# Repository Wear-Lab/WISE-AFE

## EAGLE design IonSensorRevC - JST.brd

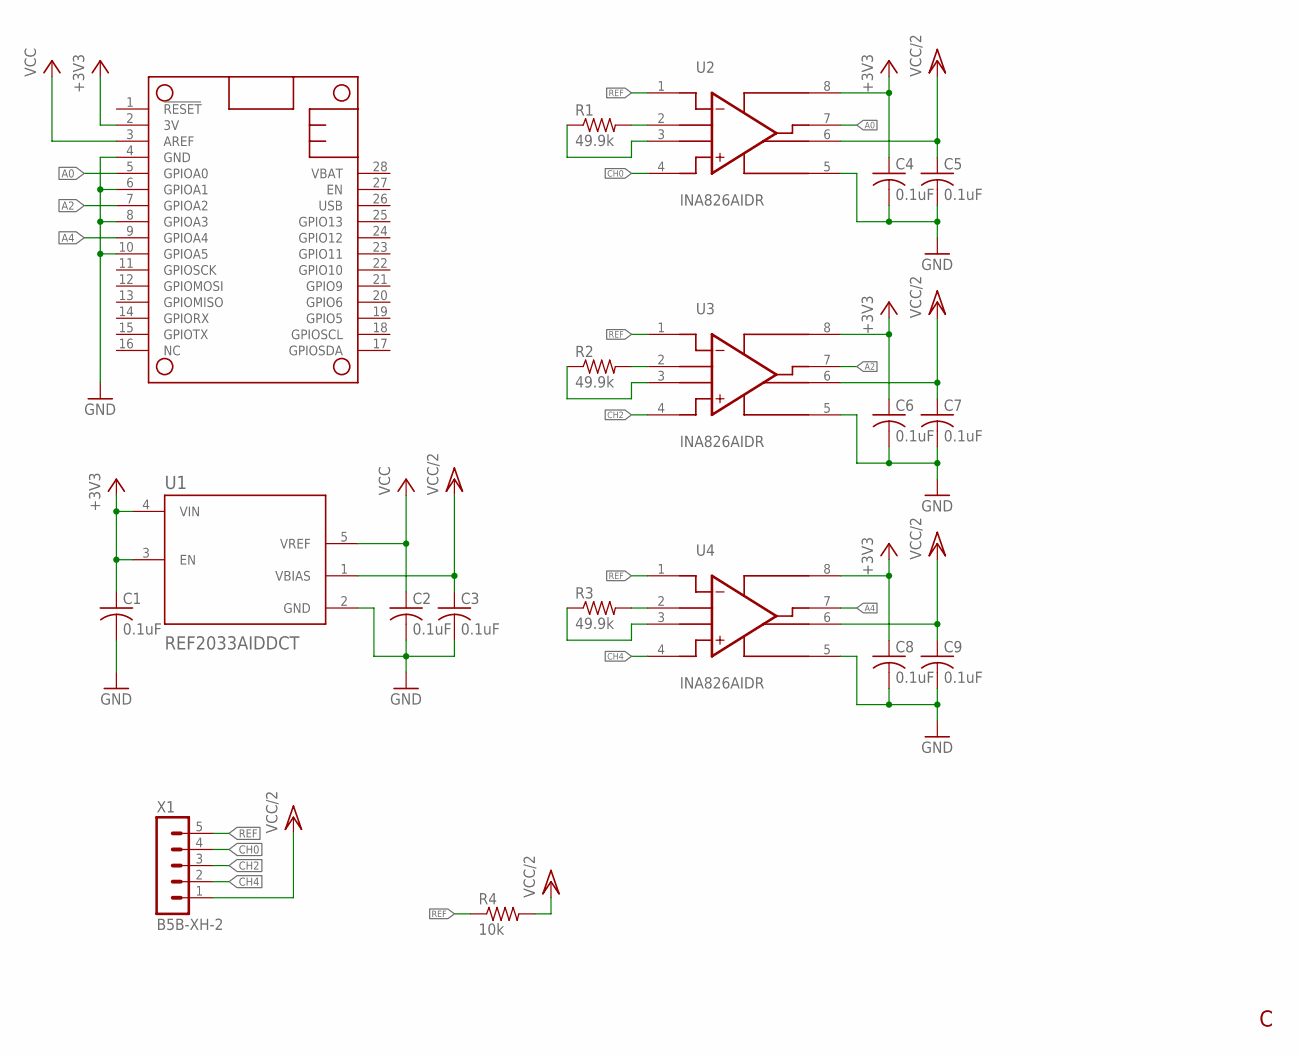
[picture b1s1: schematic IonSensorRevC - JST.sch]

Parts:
C1, C2, C3, C4, C5, C6, C7, C8, C9: 0.1uF; C0402
MS1: FEATHERWING
R1, R2, R3: 49.9k; R0402
R4: 10k; R0402
U1: REF2033AIDDCT; SOT95P280X110-5N
U2, U3, U4: INA826AIDR; SOIC127P599X175-8N
X1: B5B-XH-2; B5B-XH-A

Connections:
+3V3: C1.1, C4.1, C6.1, C8.1, MS1.2 (3V), U1.3 (EN), U1.4 (VIN), U2.8 (+VS), U3.8 (+VS), U4.8 (+VS)
A0: MS1.5 (GPIOA0), U2.7 (VOUT)
A2: MS1.7 (GPIOA2), U3.7 (VOUT)
A4: MS1.9 (GPIOA4), U4.7 (VOUT)
CH0: U2.4 (+IN), X1.4
CH2: U3.4 (+IN), X1.3
CH4: U4.4 (+IN), X1.2
GND: C1.2, C2.2, C3.2, C4.2, C5.2, C6.2, C7.2, C8.2, C9.2, MS1.4 (GND), MS1.6 (GPIOA1), MS1.8 (GPIOA3), MS1.10 (GPIOA5), U1.2 (GND), U2.5 (-VS), U3.5 (-VS), U4.5 (-VS)
unnamed: R1.2, U2.2 (RG_2)
unnamed: R1.1, U2.3 (RG_3)
unnamed: R2.2, U3.2 (RG_2)
unnamed: R2.1, U3.3 (RG_3)
unnamed: R3.2, U4.2 (RG_2)
unnamed: R3.1, U4.3 (RG_3)
REF: R4.1, U2.1 (-IN), U3.1 (-IN), U4.1 (-IN), X1.5
VCC: C2.1, MS1.3 (AREF), U1.5 (VREF)
VCC/2: C3.1, C5.1, C7.1, C9.1, R4.2, U1.1 (VBIAS), U2.6 (REF), U3.6 (REF), U4.6 (REF), X1.1

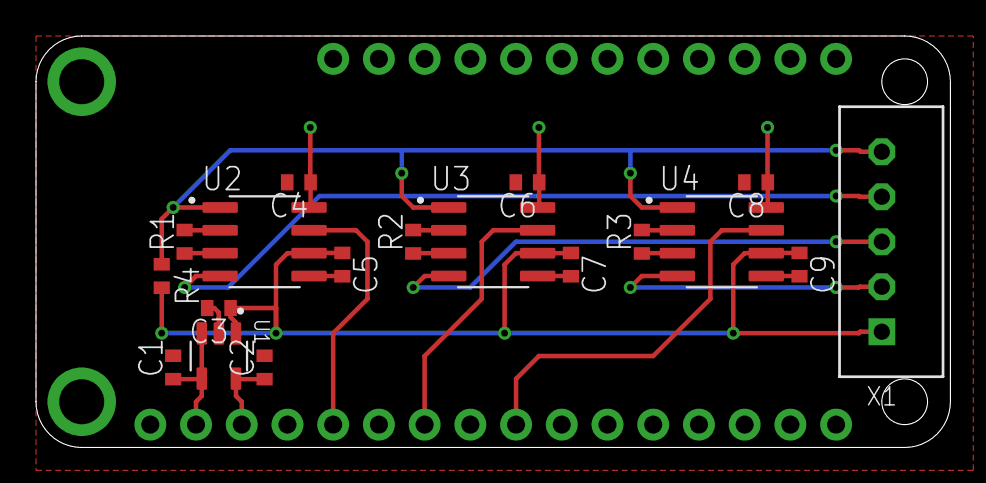
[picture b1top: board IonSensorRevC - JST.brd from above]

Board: 2 copper layers, 50.8 x 22.9 mm, 19 parts (0 on the bottom side), 17 nets.

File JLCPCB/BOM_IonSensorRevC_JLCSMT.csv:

Comment,Designator,Footprint
0.1uF,"C1, C2, C3, C4, C5, C6, C7, C8, C9",C0402
10k,R4,R0402
49.9k,"R1, R2, R3",R0402
INA826AIDR,"U2, U3, U4",SOIC127P599X175-8N
REF2033AIDDCT,U1,SOT95P280X110-5N
52745-0690,X1,52745-0690

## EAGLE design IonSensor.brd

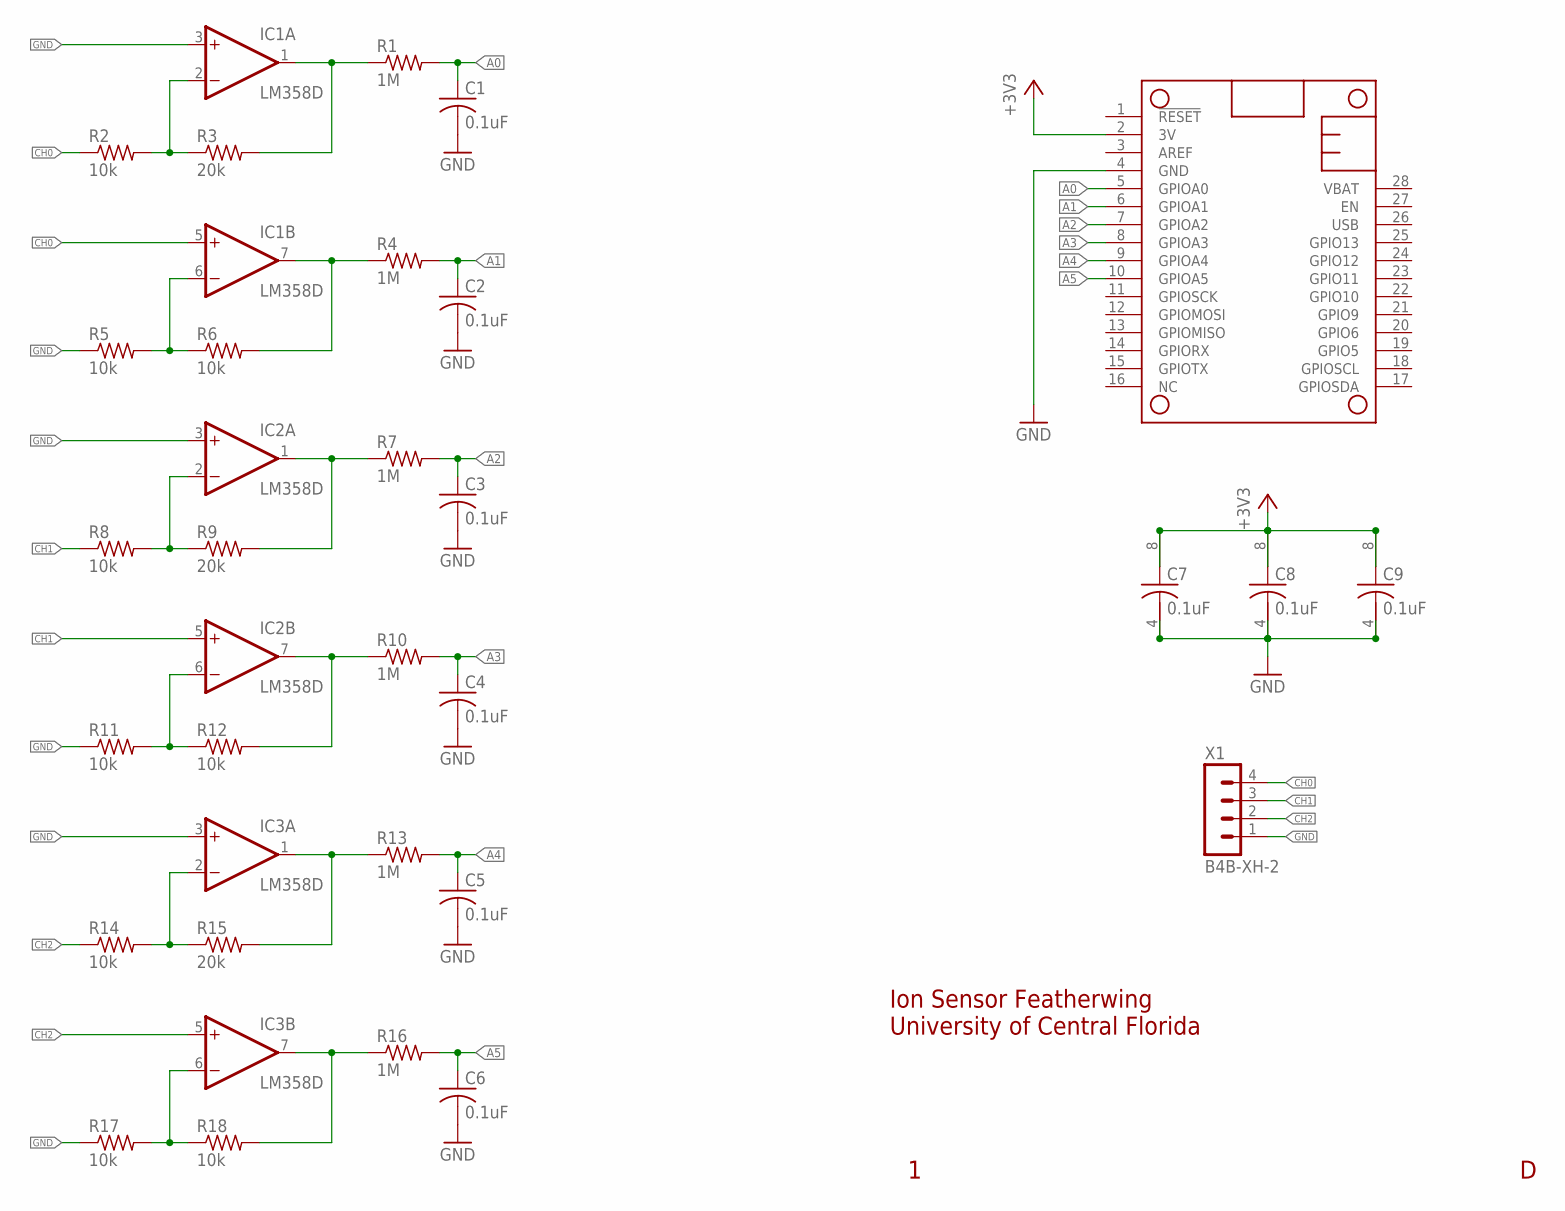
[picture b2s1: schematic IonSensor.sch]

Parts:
C1, C2, C3, C4, C5, C6, C7, C8, C9: 0.1uF; C0402
IC1, IC2, IC3: LM358D; SO08
MS1: FEATHERWING
R1, R4, R7, R10, R13, R16: 1M; R0402
R2, R5, R6, R8, R11, R12, R14, R17, R18: 10k; R0402
R3, R9, R15: 20k; R0402
X1: B4B-XH-2; B4B-XH-A

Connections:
+3V3: C7.1, C8.1, C9.1, IC1.8 (V+), IC2.8 (V+), IC3.8 (V+), MS1.2 (3V)
A0: C1.1, MS1.5 (GPIOA0), R1.2
A1: C2.1, MS1.6 (GPIOA1), R4.2
A2: C3.1, MS1.7 (GPIOA2), R7.2
A3: C4.1, MS1.8 (GPIOA3), R10.2
A4: C5.1, MS1.9 (GPIOA4), R13.2
A5: C6.1, MS1.10 (GPIOA5), R16.2
CH0: IC1.5 (+IN), R2.1, X1.4
CH1: IC2.5 (+IN), R8.1, X1.3
CH2: IC3.5 (+IN), R14.1, X1.2
GND: C1.2, C2.2, C3.2, C4.2, C5.2, C6.2, C7.2, C8.2, C9.2, IC1.3 (+IN), IC1.4 (V-), IC2.3 (+IN), IC2.4 (V-), IC3.3 (+IN), IC3.4 (V-), MS1.4 (GND), R5.1, R11.1, R17.1, X1.1
unnamed: IC1.2 (-IN), R2.2, R3.1
unnamed: IC1.6 (-IN), R5.2, R6.1
unnamed: IC1.1 (OUT), R1.1, R3.2
unnamed: IC1.7 (OUT), R4.1, R6.2
unnamed: IC2.2 (-IN), R8.2, R9.1
unnamed: IC2.1 (OUT), R7.1, R9.2
unnamed: IC2.6 (-IN), R11.2, R12.1
unnamed: IC2.7 (OUT), R10.1, R12.2
unnamed: IC3.2 (-IN), R14.2, R15.1
unnamed: IC3.1 (OUT), R13.1, R15.2
unnamed: IC3.6 (-IN), R17.2, R18.1
unnamed: IC3.7 (OUT), R16.1, R18.2

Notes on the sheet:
Ion Sensor Featherwing University of Central Florida

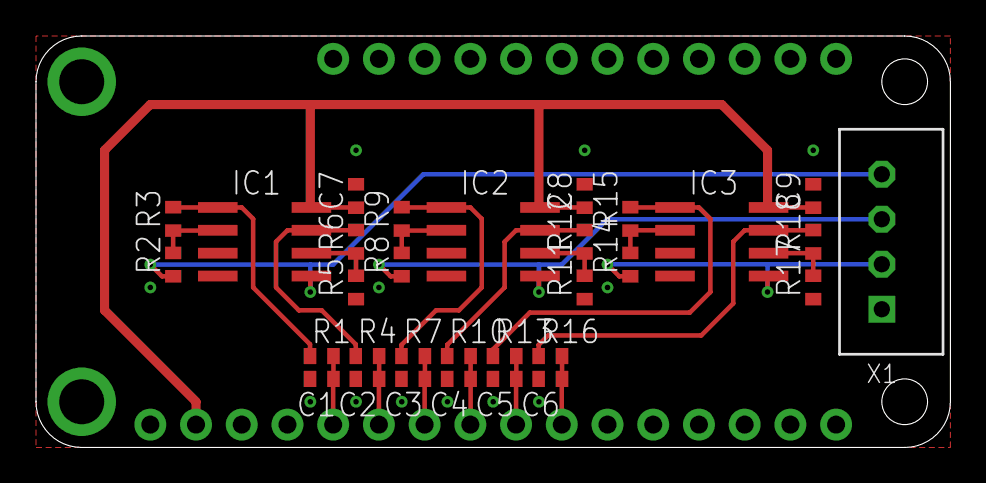
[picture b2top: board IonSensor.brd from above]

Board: 2 copper layers, 50.8 x 22.9 mm, 32 parts (0 on the bottom side), 23 nets.

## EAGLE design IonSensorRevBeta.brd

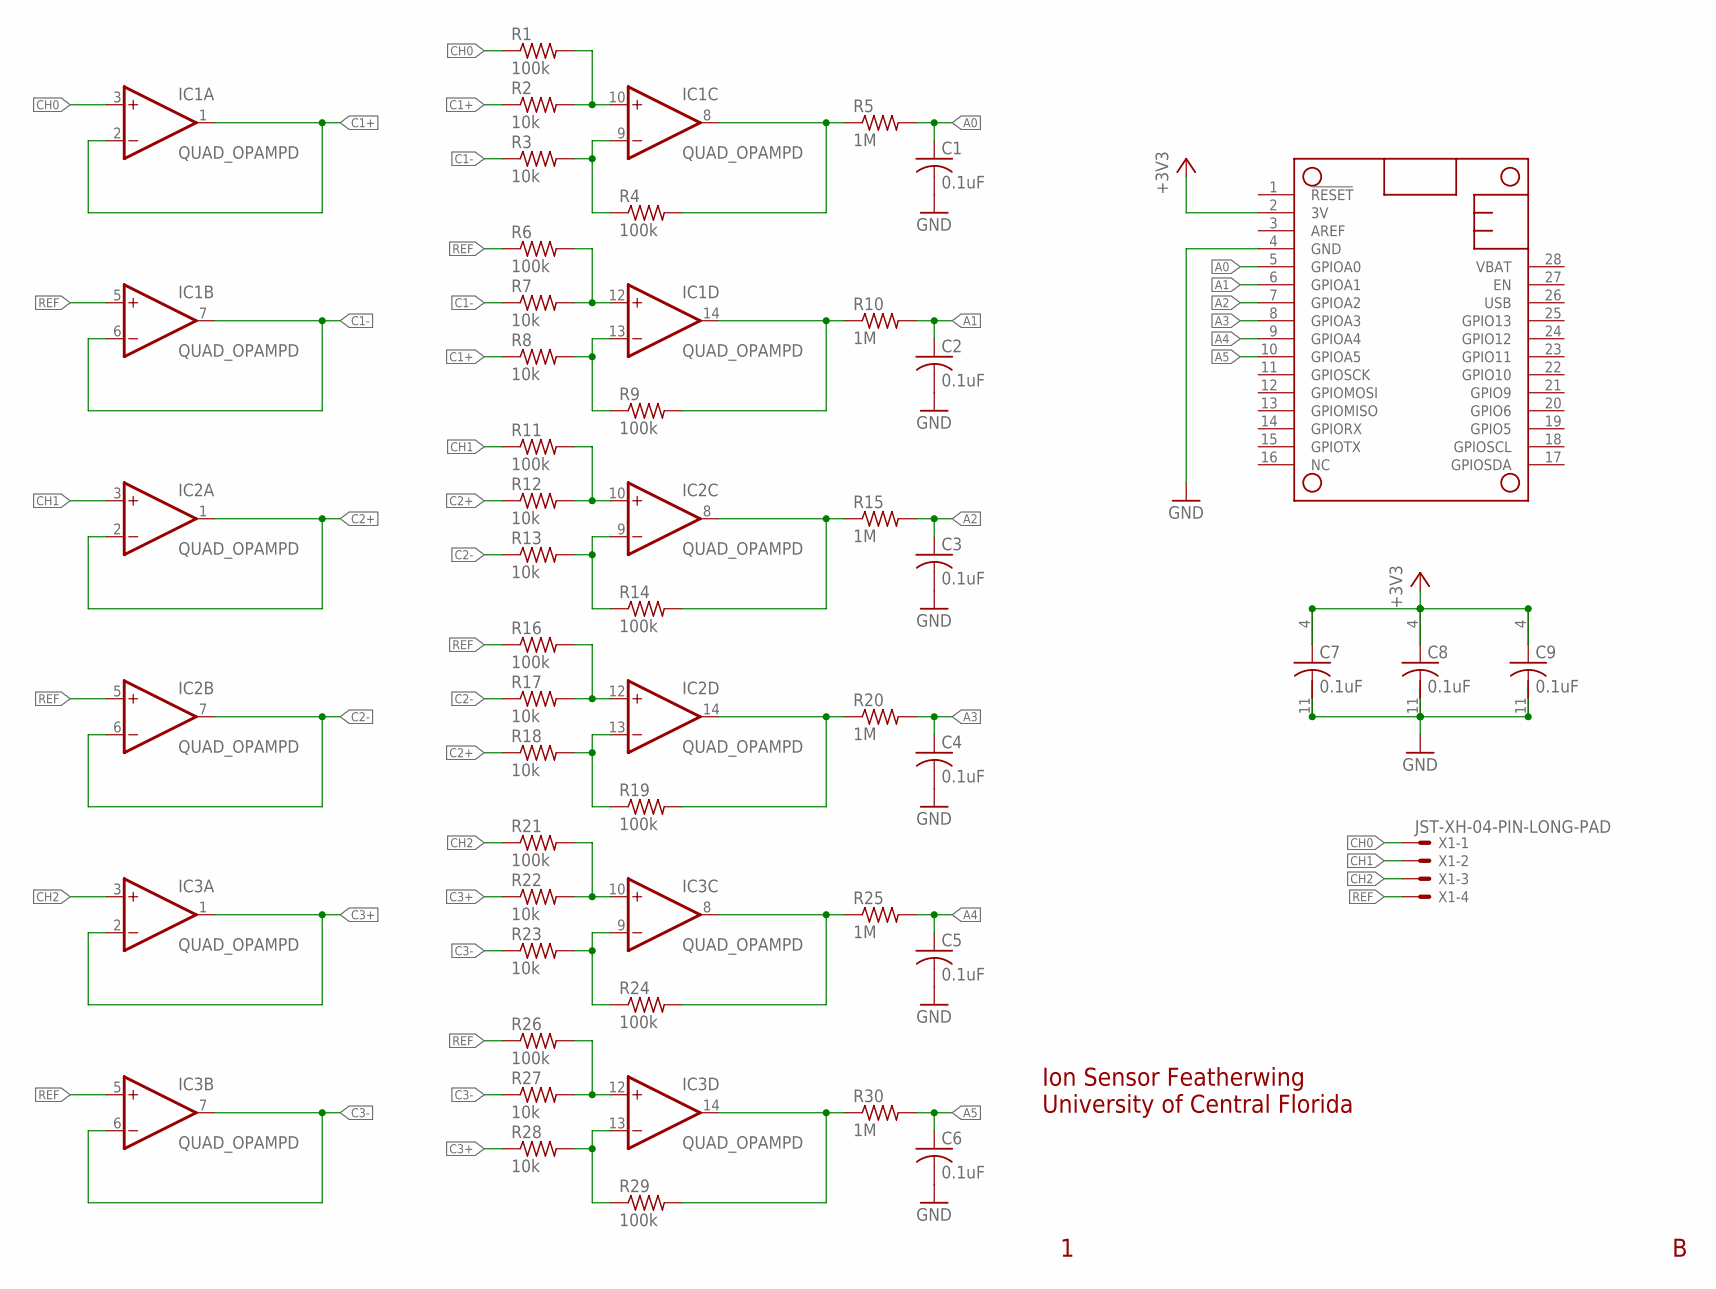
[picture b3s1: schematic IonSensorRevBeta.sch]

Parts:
C1, C2, C3, C4, C5, C6, C7, C8, C9: 0.1uF; C0402
IC1, IC2, IC3: QUAD_OPAMPD; SO14
MS1: FEATHERWING
R1, R4, R6, R9, R11, R14, R16, R19, R21, R24, R26, R29: 100k; R0402
R2, R3, R7, R8, R12, R13, R17, R18, R22, R23, R27, R28: 10k; R0402
R5, R10, R15, R20, R25, R30: 1M; R0402
X1: JST-XH-04-PIN-LONG-PAD; JST-XH-04-PACKAGE-LONG-PAD

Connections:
+3V3: C7.1, C8.1, C9.1, IC1.4 (V+), IC2.4 (V+), IC3.4 (V+), MS1.2 (3V)
A0: C1.1, MS1.5 (GPIOA0), R5.2
A1: C2.1, MS1.6 (GPIOA1), R10.2
A2: C3.1, MS1.7 (GPIOA2), R15.2
A3: C4.1, MS1.8 (GPIOA3), R20.2
A4: C5.1, MS1.9 (GPIOA4), R25.2
A5: C6.1, MS1.10 (GPIOA5), R30.2
C1+: IC1.1 (OUT), IC1.2 (-IN), R2.1, R8.1
C1-: IC1.6 (-IN), IC1.7 (OUT), R3.1, R7.1
C2+: IC2.1 (OUT), IC2.2 (-IN), R12.1, R18.1
C2-: IC2.6 (-IN), IC2.7 (OUT), R13.1, R17.1
C3+: IC3.1 (OUT), IC3.2 (-IN), R22.1, R28.1
C3-: IC3.6 (-IN), IC3.7 (OUT), R23.1, R27.1
CH0: IC1.3 (+IN), R1.1, X1.1
CH1: IC2.3 (+IN), R11.1, X1.2
CH2: IC3.3 (+IN), R21.1, X1.3
GND: C1.2, C2.2, C3.2, C4.2, C5.2, C6.2, C7.2, C8.2, C9.2, IC1.11 (V-), IC2.11 (V-), IC3.11 (V-), MS1.4 (GND)
unnamed: IC1.10 (+IN), R1.2, R2.2
unnamed: IC1.9 (-IN), R3.2, R4.1
unnamed: IC3.10 (+IN), R21.2, R22.2
unnamed: IC1.12 (+IN), R6.2, R7.2
unnamed: IC1.8 (OUT), R4.2, R5.1
unnamed: IC1.13 (-IN), R8.2, R9.1
unnamed: IC3.9 (-IN), R23.2, R24.1
unnamed: IC2.10 (+IN), R11.2, R12.2
unnamed: IC2.9 (-IN), R13.2, R14.1
unnamed: IC1.14 (OUT), R9.2, R10.1
unnamed: IC2.12 (+IN), R16.2, R17.2
unnamed: IC3.12 (+IN), R26.2, R27.2
unnamed: IC2.13 (-IN), R18.2, R19.1
unnamed: IC2.8 (OUT), R14.2, R15.1
unnamed: IC3.13 (-IN), R28.2, R29.1
unnamed: IC2.14 (OUT), R19.2, R20.1
unnamed: IC3.8 (OUT), R24.2, R25.1
unnamed: IC3.14 (OUT), R29.2, R30.1
REF: IC1.5 (+IN), IC2.5 (+IN), IC3.5 (+IN), R6.1, R16.1, R26.1, X1.4

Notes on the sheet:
Ion Sensor Featherwing University of Central Florida

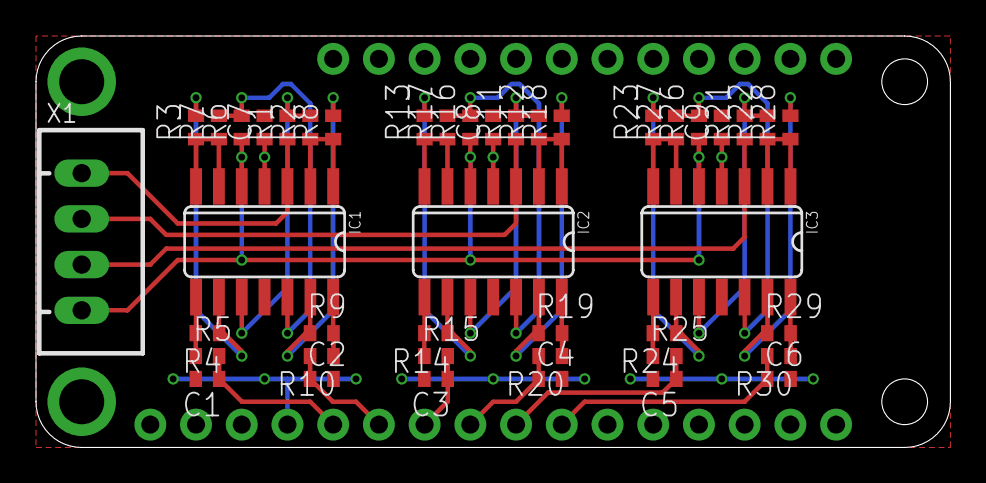
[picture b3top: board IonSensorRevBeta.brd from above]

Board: 2 copper layers, 50.8 x 22.9 mm, 44 parts (0 on the bottom side), 36 nets.

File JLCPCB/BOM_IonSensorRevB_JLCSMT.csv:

Comment,Designator,Footprint
0.1uF,"C1,C2,C3,C4,C5,C6,C7,C8,C9",C0402
100k,"R1,R4,R6,R9,R11,R14,R16,R19,R21,R24,R26,R29",R0402
10k,"R2,R3,R7,R8,R12,R13,R17,R18,R22,R23,R27,R28",R0402
1M,"R5,R10,R15,R20,R25,R30",R0402
QUAD_OPAMPD,"IC1,IC2,IC3",SO14
F0500WR-S-04PNLNG1GT0R,X1,F0500WR-S-04PNLNG1GT0R

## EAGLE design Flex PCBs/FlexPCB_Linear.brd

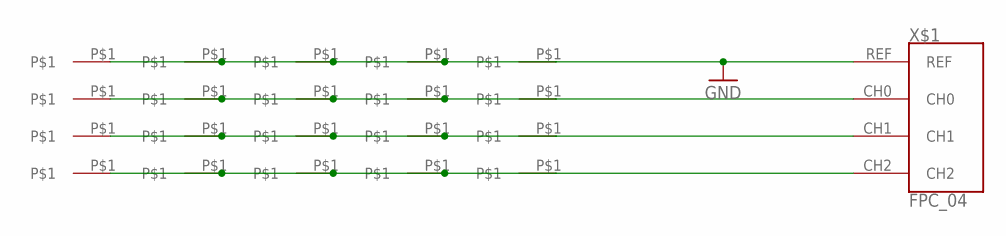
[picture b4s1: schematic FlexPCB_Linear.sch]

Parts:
U$1, U$2, U$3, U$4, U$5, U$6, U$7, U$8, U$9, U$10, U$11, U$12, U$13, U$14, U$15, U$16, U$17, U$18, U$19, U$20: CONN
X$1: FPC_04

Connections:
GND: U$1.P$1, U$5.P$1, U$9.P$1, U$13.P$1, U$17.P$1, X$1.REF
unnamed: U$2.P$1, U$6.P$1, U$10.P$1, U$14.P$1, U$18.P$1, X$1.CH0
unnamed: U$3.P$1, U$7.P$1, U$11.P$1, U$15.P$1, U$19.P$1, X$1.CH1
unnamed: U$4.P$1, U$8.P$1, U$12.P$1, U$16.P$1, U$20.P$1, X$1.CH2

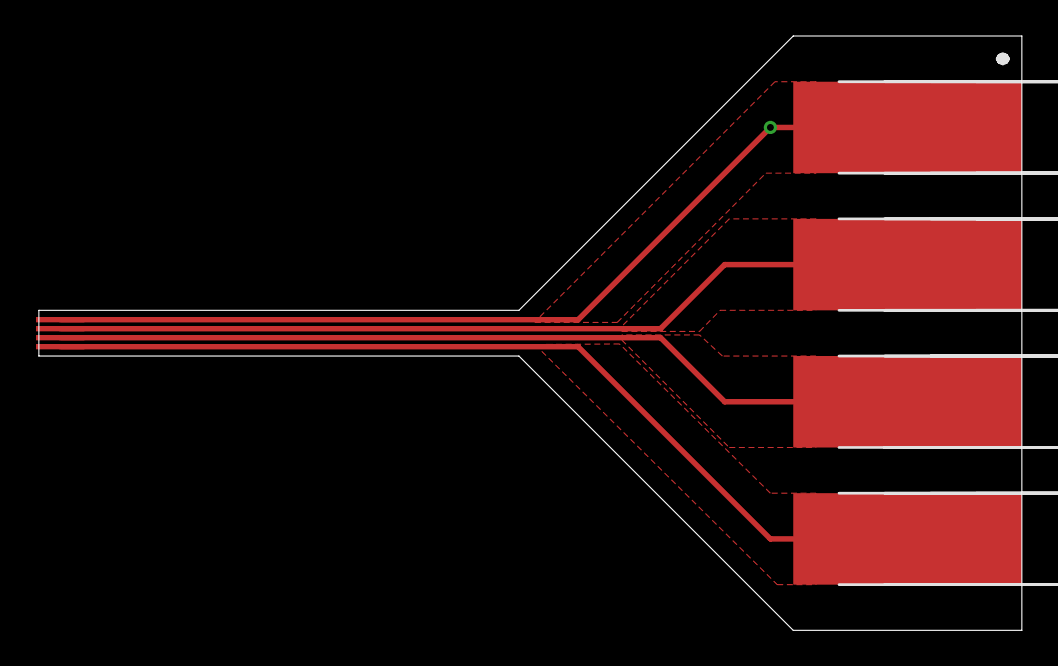
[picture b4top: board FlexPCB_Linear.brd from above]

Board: 2 copper layers, 54.6 x 33.0 mm, 21 parts (0 on the bottom side), 4 nets.

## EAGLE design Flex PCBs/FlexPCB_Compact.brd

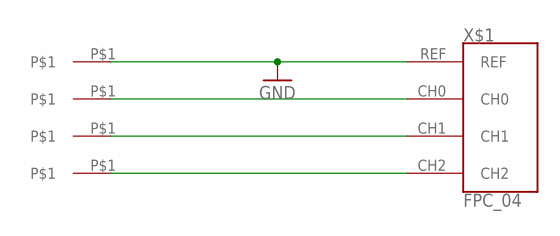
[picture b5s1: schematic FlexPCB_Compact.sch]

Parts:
CH0, CH1, CH2: CONN
REF: CONN
X$1: FPC_04

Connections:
GND: REF.P$1, X$1.REF
unnamed: CH0.P$1, X$1.CH0
unnamed: CH1.P$1, X$1.CH1
unnamed: CH2.P$1, X$1.CH2

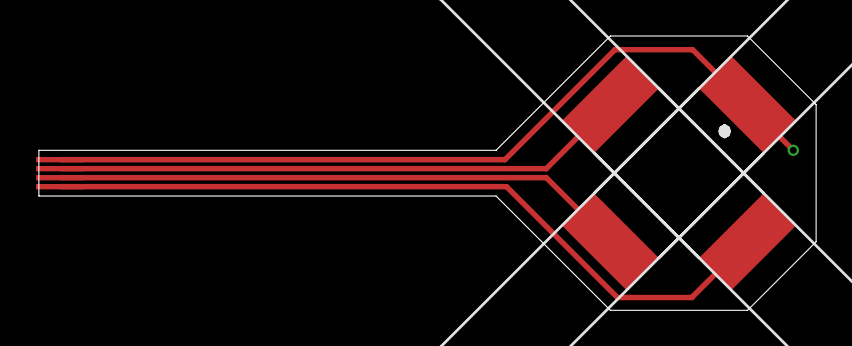
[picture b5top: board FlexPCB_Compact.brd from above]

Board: 2 copper layers, 43.2 x 15.2 mm, 5 parts (0 on the bottom side), 4 nets.

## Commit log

2023-02-27 Initial Commit
    Mirror of RevC
2023-03-06 Update traces
    Updated traces to minimize noise
2023-06-05 Revert to modified Rev A
    Revert to modified Rev A, using JST-XH. Positive channel reading only.
2023-06-07 Fixed wiring
    Made sure it's a differential amplifier!
    Removed R13.
2023-06-07 Update eagle.epf
    Just closed Eagle project file, should update .epf
2023-06-07 Rev. D
    Upgrade to Rev. D, no connector
2023-06-10 Added JST XH Connector
    Added JST XH connector. TODO: Wire channels up!
2023-06-10 Routing complete
    Completed routing for Rev. D
2023-06-13 Revert "Routing complete"
    This reverts commit f47511b647111c71903cb3d4dec75a0fe3392e94.
2023-06-13 Revert "Added JST XH Connector"
    This reverts commit 28e9dc296f10d82968848f6f33b36970200c6171.
2023-06-13 Revert "Rev. D"
    This reverts commit b0cd00c38bcd6b0f7db002c888a5e278bdb202ce.
2023-06-23 Switch to 2 channel opamp
    Switched to 2 channel opamp instead of quad opamp.
2023-06-26 JLCSMT
    Added JLCSMT files
2023-09-19 Revert "JLCSMT"
    This reverts commit ff1b805373eafdff03922dc39232167e1a6e9073.
2023-09-19 Revert "Switch to 2 channel opamp"
    This reverts commit d2c6276b5e9005aaa4bb267ec01d57cf95291150.
2023-09-19 Revert "Update eagle.epf"
    This reverts commit c819467c6d0d7514130f73769fe2b53bb764558c.
2023-09-19 Revert "Fixed wiring"
    This reverts commit 887158206b74e515af25e9af216689274ec85624.
2023-09-19 Revert "Revert to modified Rev A"
    This reverts commit f9afd16b8134e14ecb11c0382d33eae065ec5b6d.
